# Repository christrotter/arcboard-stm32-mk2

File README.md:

# arcboard-stm32-mk2

Next iteration of the [STM32F405 mainboard](https://github.com/christrotter/arcboard-stm32).

## Features
- STM32F407 w. 12mHz HSE crystal
- 60x60mm footprint
- **60-pin FFC connector** for [the bespoke FFC loom](https://github.com/christrotter/arcboard-mk22-ffc)
  - Connects: 3x encoders, 4x6 keywell & 5 thumb keys, dpad, 3x paddle buttons, LCD, indicator LED PCBs, PMW3360
- **onboard button** for reset(*momentary*) and boot(*hold*) (*remote output also*)
- 128mb external **flash** via SPI (16MB)
- DRV2605L **haptic** driver via I2C, with PWM trigger (LRA or ERM)
- PAM8302A 2.5w **amplifier & piezo** (*or outputs*)
- 32kHz LSE crystal & **VBAT** wiring (*via external 1.8-3.3v battery*)
- **Two-layer** PCB & PCBA design for more affordable manufacturing
- Both USB connections have **ESD & power protection**
- Designed for **remote-mount** USB ports and boot/reset button
- **Split hand** GPIO via solder jumper
- **VBUS detection** via GPIO
- RGB-5v and LCD-3.3v supplies through MOSFET w. GPIO triggers
- WS2812 signal **level-shifted** to 5v
- Optional outputs
  - I2C
  - Debug
  - Haptic
  - Amplifier out
  - Ground + RGB-5v + WS2812 chain (*continuing from main loom*) for adding more LEDs (*e.g. aesthetic, underglow, etc*)
  - **Limit switch** (pull-up) output

## Improvements
- 100-pin CPU package offers much more flexibility, more options when wiring up the board
- The only soldering required is for JST-PH connectors (*2.0mm pin spacing*)
- Smaller diode package and setup saves space, keeps us on two-layer
- Actually working DFU system this time (*bad LCD pcb caused problems*)
- Fixed a number of issues, including mysterious overheating caused by a poor quality Schottky diode (*and bad spec choice on my part*)
- Inkscape-designed back silkscreen

## QMK notes
- I'm using `ROW2COL` because the Cyboard pcb's are designed this way.

## PCB/PCBA cost
My costs for getting the board made and assembled by JLC, to give you an idea of what this would cost to have built for you.

| Item | Cost (CAD) |
|---|---:|
| Setup fee | $25.56 |
| Stencil | $8.21 |
| Components | $67.86 |
| Extended components fee | $53.55 |
| SMT Assembly | $3.75 |
| Packaging fee | $0.49 |
| Advanced Options | $0.82 |
| Confirm Parts Placement | $0.45 |

## Bill of Materials (BOM)

| Designator | Footprint | Quantity | Value | LCSC Part # |
|---|---|---:|---|---|
| C1, C10, C20, C23 | 0805 | 4 | 4.7uF | C1779 |
| C11, C12, C14, C17, C18, C19, C26, C28, C5, C7, C8, C9 | 0402 | 12 | 100nF | C1525 |
| C13, C15, C2, C24, C27, C4 | 0402 | 6 | 1uF | C52923 |
| C16, C21 | 0402 | 2 | 2.2uF | C12530 |
| C22 | C0603 | 1 | CL10A106MA8NRNC | C96446 |
| C25 | C0805 | 1 | GCM21BR70J106KE22L | C126230 |
| C29, C3, C30, C6 | 0402 | 4 | 12p | C1547 |
| D1 | SMA_L4.3-W2.6-LS5.2-RD | 1 | SS34 | C8678 |
| D10, D11, D2, D3, D6, D8, D9 | X1-DFN1006-2_L1.0-W0.6-RD | 7 | CDSQC4148-HF | C6341459 |
| D4 | SOD-123FL_L2.8-W1.8-LS3.7-BI | 1 | SMF5_0CA_C364279 | C364279 |
| D5, D7 | SOT-666-6_L1.6-W1.2-P0.50-LS1.6-BL | 2 | USBLC6-2P6_C2827693 | C2827693 |
| F2 | F1206 | 1 | 1206L150SLYR | C207037 |
| F3 | F1206 | 1 | MF-NSMF075-2 | C89653 |
| L1 | L0805 | 1 | MPZ2012S101AT000 | C15957 |
| LED-LVL1 | SOT-563_L1.6-W1.2-P0.50-LS1.6-BR | 1 | SN74LVC1T45DRL | C352970 |
| MOSFET1, MOSFET3, MOSFET4 | SOT-23_L2.9-W1.3-P1.90-LS2.4-BR | 3 | AO3401A | C15127 |
| R1 | 0402 | 1 | 0402WGF1004TCE | C26083 |
| R10 | 0402 | 1 | 5.1k | C25905 |
| R11, R12, R16, R17, R2, R3, R5 | 0402 | 7 | 10k | C25744 |
| R4, R7, R8 | R0402 | 3 | 0402WGF4701TCE | C25900 |
| R14 | 0402 | 1 | 0402WGF1000TCE | C25076 |
| R15 | 0402 | 1 | 0402WGF1001TCE | C11702 |
| R6 | R0603 | 1 | 0603WAF3303T5E | C23137 |
| R9 | 0402 | 1 | 0402WGF1003TCE | C25741 |
| U1 | SOT-23-5 | 1 | XC6210B332MR-G | C82942 |
| U10, U9 | SOT-23-3_L2.9-W1.3-P1.90-LS2.4-BR | 2 | MMUN2233LT1G | C86932 |
| U13, U4 | SOT-23-3_L2.9-W1.3-P1.90-LS2.4-BR | 2 | 2N7002 | C8545 |
| U14 | SOIC-8_L5.3-W5.3-P1.27-LS8.0-BL | 1 | W25Q128JVSIQTR | C97521 |
| U15 | SW-SMD_4P-L5.1-W5.1-P3.70-LS6.5-TL_H1.5 | 1 | TS-1187A-B-A-B | C318884 |
| U2 | LQFP-100_14x14mm_P0.5mm | 1 | STM32F407VGTx | C12345 |
| U3 | FPC-SMD_FH52-60S-0.5SH | 1 | FH52-60S-0_5SH | C224193 |
| U5 | VSSOP-10_L3.0-W3.0-P0.50-LS4.9-BL | 1 | DRV2605LDGSR | C527464 |
| U6 | MSOP-8_L3.0-W3.0-P0.65-LS5.0-BL | 1 | PAM8302AASCR | C113367 |
| U8 | OSC-SMD_L3.2-W1.5 | 1 | SC-32S32_768kHz20PPM7pF | C97604 |
| Y1 | CRYSTAL-SMD_4P-L3.2-W2.5-BL-1 | 1 | Crystal_GND24 | C9002 |

Total line items: 35  
Total component quantity: 77

## Renders

## PCB layout

## Schematic

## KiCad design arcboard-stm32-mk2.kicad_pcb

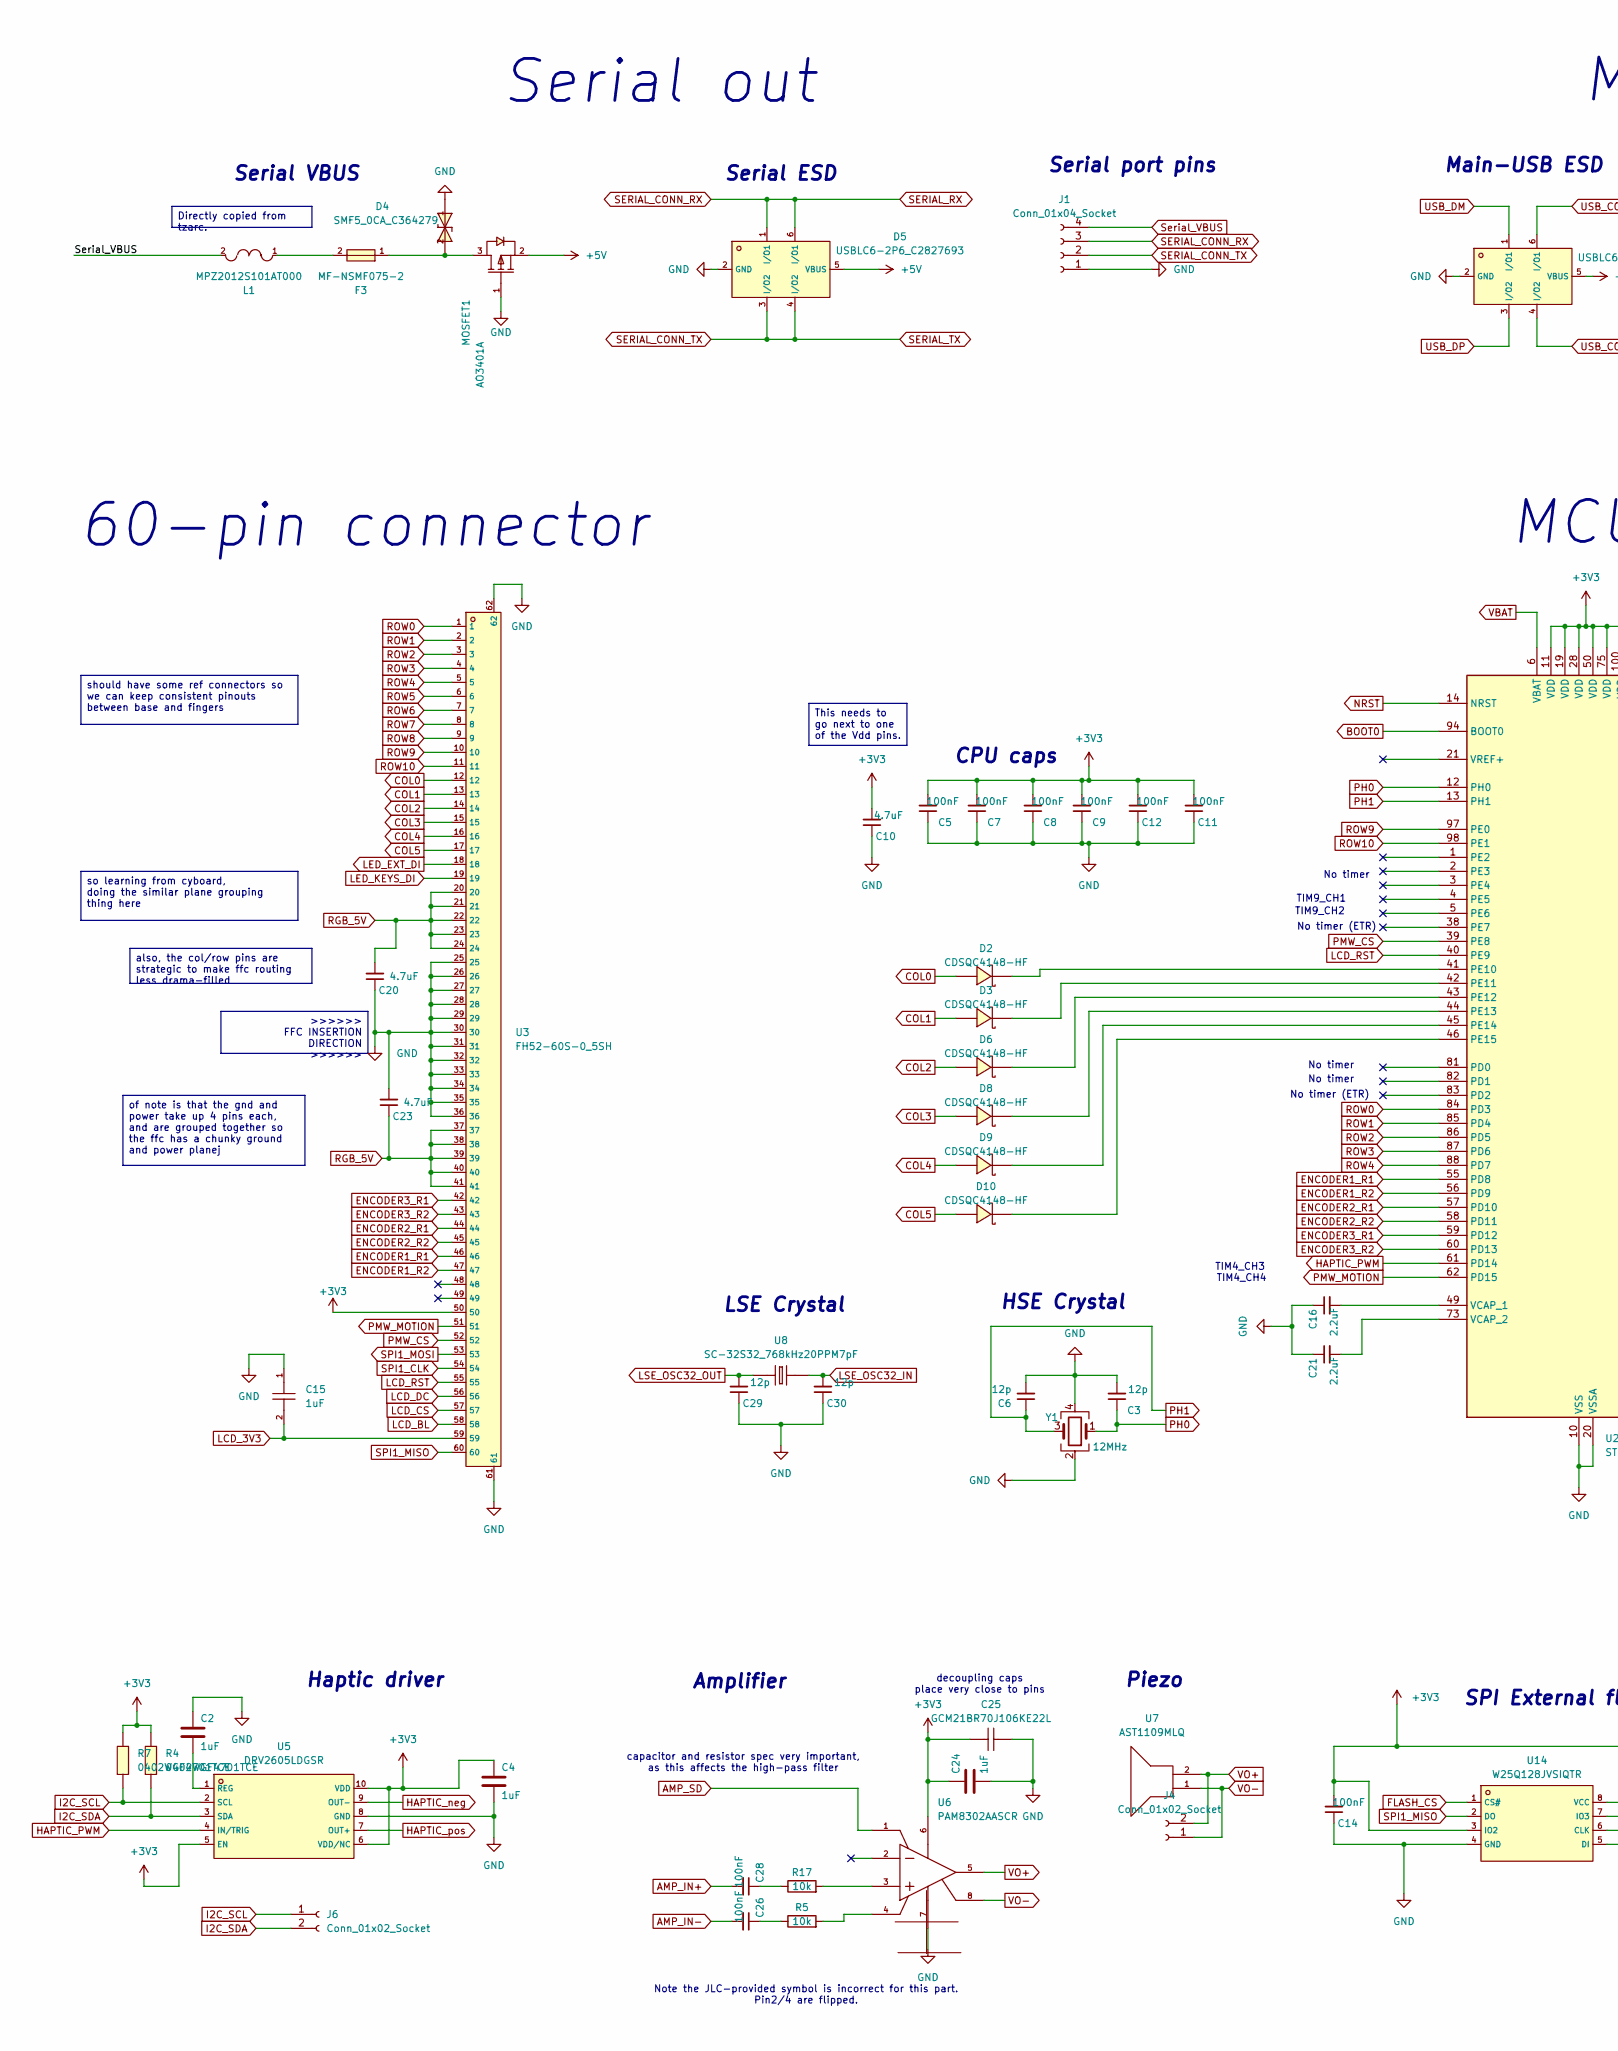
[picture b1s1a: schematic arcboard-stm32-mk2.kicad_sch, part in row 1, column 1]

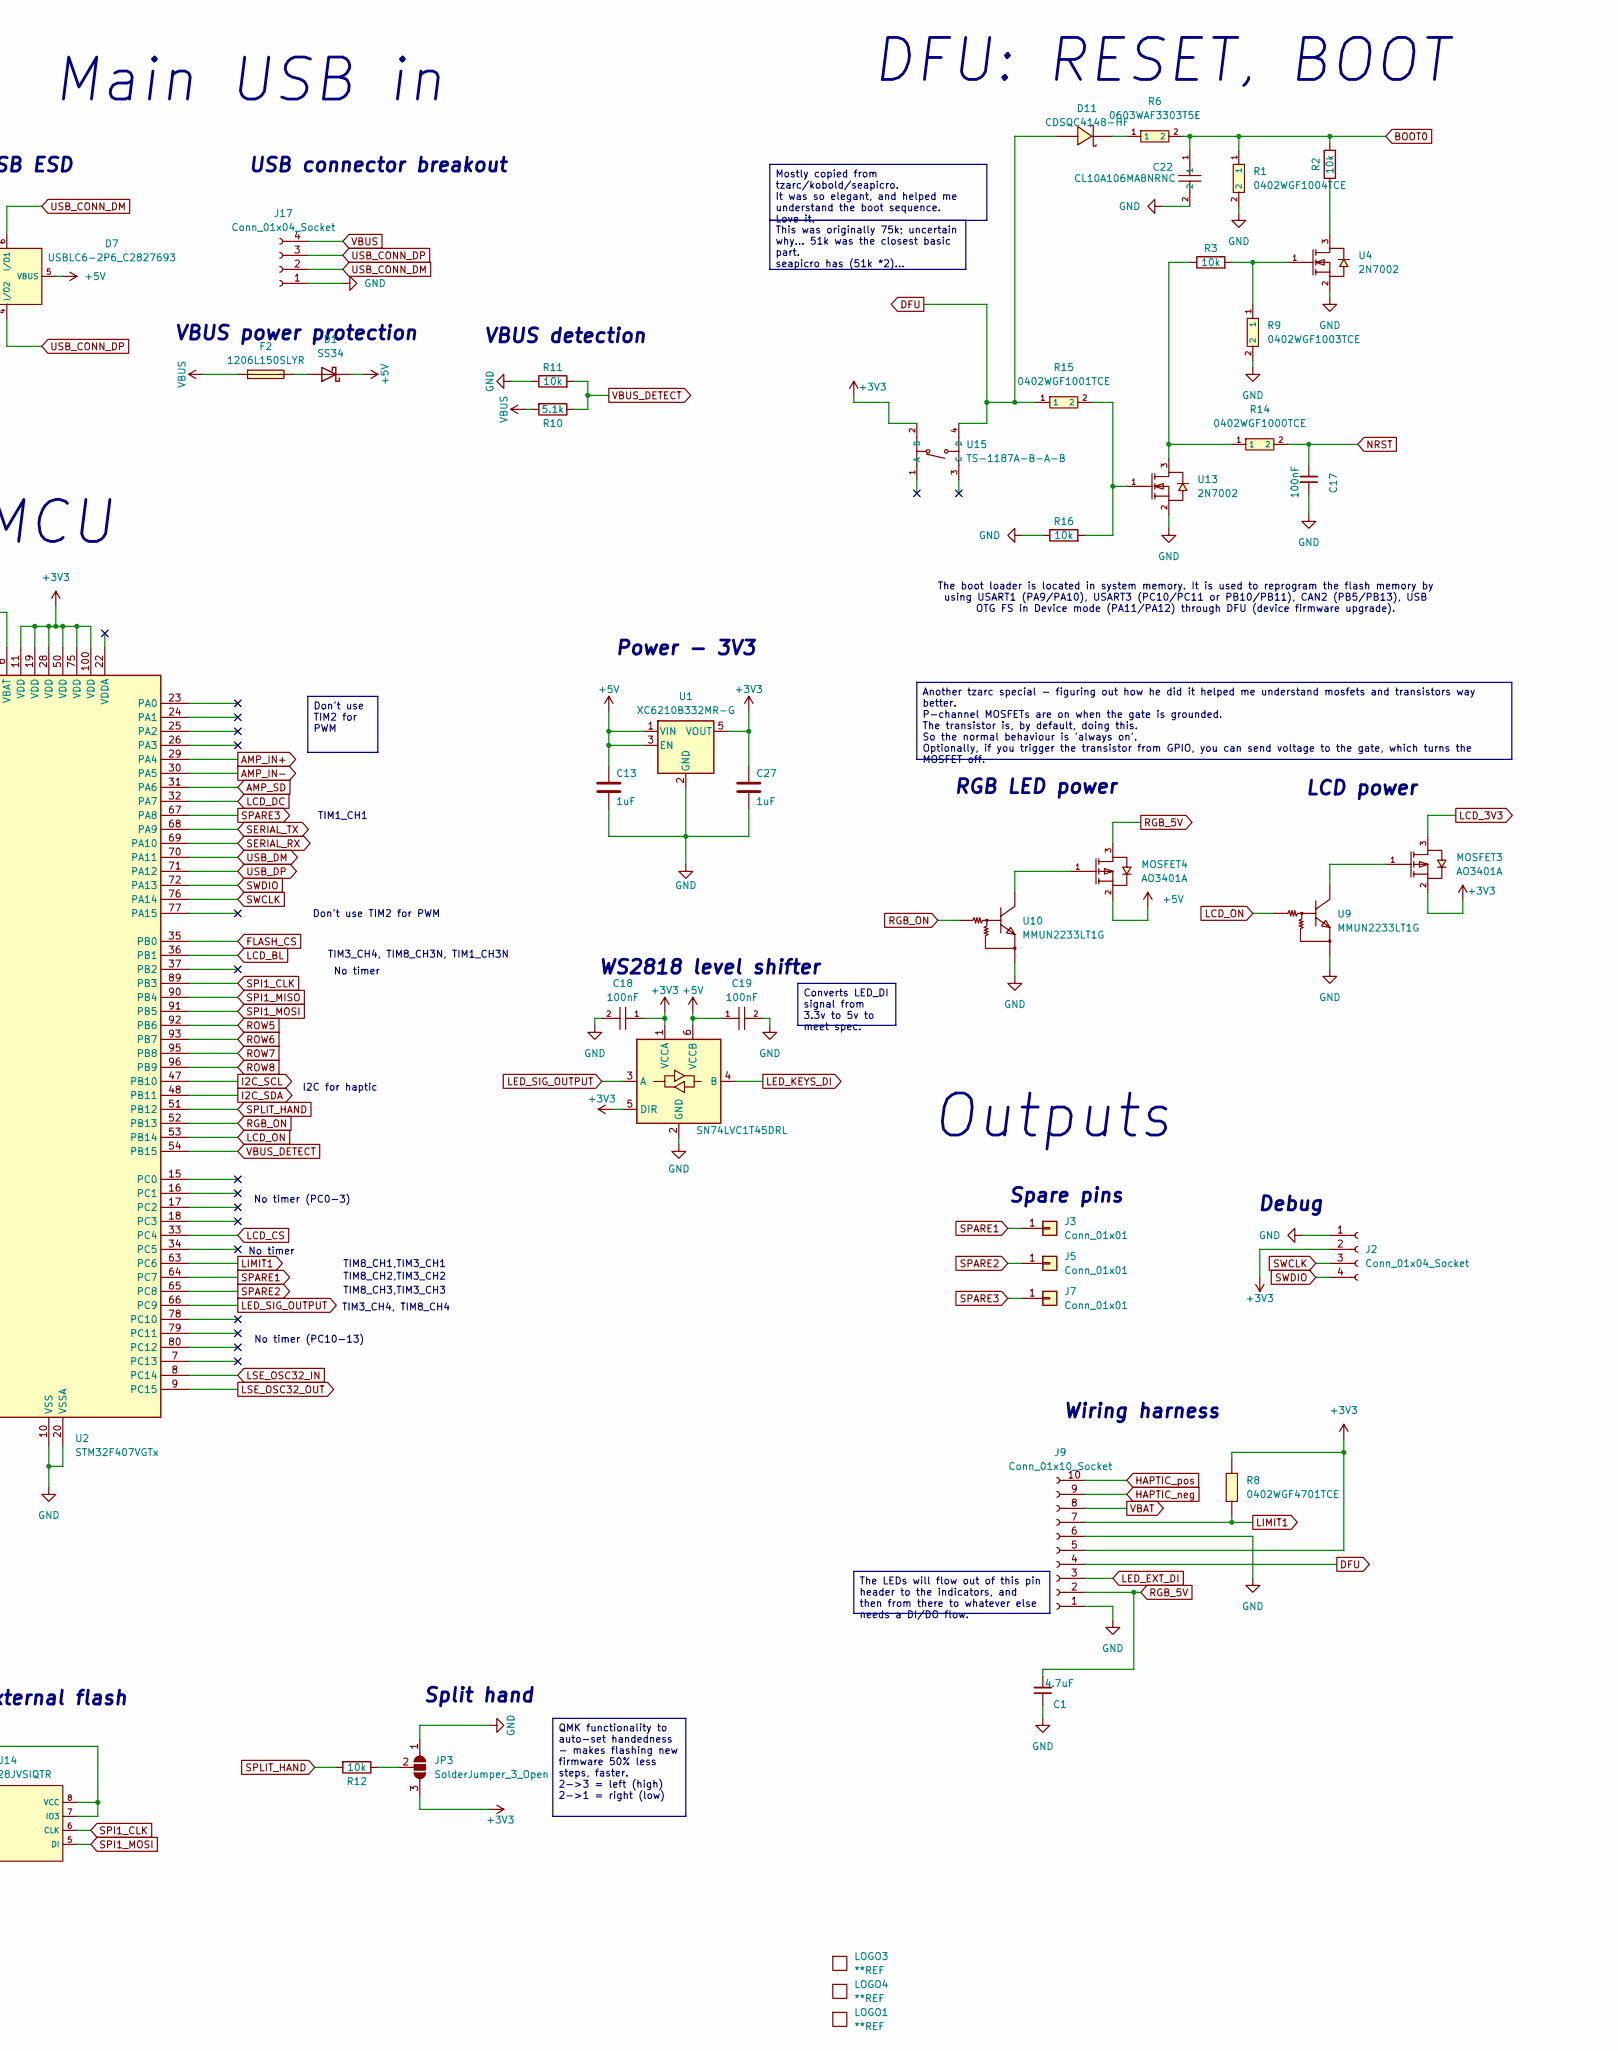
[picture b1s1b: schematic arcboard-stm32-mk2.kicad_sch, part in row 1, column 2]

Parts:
C1, C10, C20, C23: 4.7uF; C_0805_2012Metric; LCSC C1779
C2, C4, C13, C15, C24, C27: 1uF; C_0402_1005Metric; LCSC C52923
C3, C6, C29, C30: 12p; C_0402_1005Metric; LCSC C1547
C5, C7, C8, C9, C11, C12, C14, C17, C18, C19, C26, C28: 100nF; C_0402_1005Metric; LCSC C1525
C16, C21: 2.2uF; C_0402_1005Metric; LCSC C12530
C22: CL10A106MA8NRNC; C0603; LCSC C96446
C25: GCM21BR70J106KE22L; C0805; LCSC C126230
D1: SS34; SMA_L4.3-W2.6-LS5.2-RD; LCSC C8678
D2, D3, D6, D8, D9, D10, D11: CDSQC4148-HF; X1-DFN1006-2_L1.0-W0.6-RD; LCSC C6341459
D4: SMF5_0CA_C364279; SOD-123FL_L2.8-W1.8-LS3.7-BI; LCSC C364279
D5, D7: USBLC6-2P6_C2827693; SOT-666-6_L1.6-W1.2-P0.50-LS1.6-BL; LCSC C2827693
F2: 1206L150SLYR; F1206; LCSC C207037
F3: MF-NSMF075-2; F1206; LCSC C89653
J1, J17: Conn_01x04_Socket; JST_PH_S4B-PH-K_1x04_P2.00mm_Horizontal
J2: Conn_01x04_Socket; PinSocket_1x04_P1.00mm_Vertical
J3, J5, J7: Conn_01x01; TestPoint_Pad_1.5x1.5mm
J4: Conn_01x02_Socket; JST_PH_S2B-PH-K_1x02_P2.00mm_Horizontal
J6: Conn_01x02_Socket; PinHeader_1x02_P1.00mm_Vertical
J9: Conn_01x10_Socket; JST_PH_S10B-PH-K_1x10_P2.00mm_Horizontal
JP3: SolderJumper_3_Open; SolderJumper-3_P1.3mm_Open_Pad1.0x1.5mm
L1: MPZ2012S101AT000; L0805; LCSC C15957
LED-LVL1: SN74LVC1T45DRL; SOT-563_L1.6-W1.2-P0.50-LS1.6-BR; MPN SN74LVC1T45DRLR; JLC Basic N
LOGO1: **REF; awesome-logo
LOGO3: **REF; cyboard-logo-10mm
LOGO4: **REF; qmk-lite
MOSFET1, MOSFET3, MOSFET4: AO3401A; SOT-23_L2.9-W1.3-P1.90-LS2.4-BR; LCSC C15127
R1: 0402WGF1004TCE; R_0402_1005Metric; LCSC C26083
R2, R3, R5, R11, R12, R16, R17: 10k; R_0402_1005Metric; LCSC C25744
R4, R7, R8: 0402WGF4701TCE; R0402; LCSC C25900
R6: 0603WAF3303T5E; R0603; LCSC C23137
R9: 0402WGF1003TCE; R_0402_1005Metric; LCSC C25741
R10: 5.1k; R_0402_1005Metric; LCSC C25905
R14: 0402WGF1000TCE; R_0402_1005Metric; LCSC C25076
R15: 0402WGF1001TCE; R_0402_1005Metric; LCSC C11702
U1: XC6210B332MR-G; SOT-23-5; LCSC C82942
U2: STM32F407VGTx; LQFP-100_14x14mm_P0.5mm; LCSC C12345
U3: FH52-60S-0_5SH; FPC-SMD_FH52-60S-0.5SH; LCSC C224193
U4, U13: 2N7002; SOT-23-3_L2.9-W1.3-P1.90-LS2.4-BR; LCSC C8545
U5: DRV2605LDGSR; VSSOP-10_L3.0-W3.0-P0.50-LS4.9-BL; LCSC C527464
U6: PAM8302AASCR; MSOP-8_L3.0-W3.0-P0.65-LS5.0-BL; LCSC C113367
U7: AST1109MLQ; BUZ-SMD_L11.0-W9.0; LCSC C9900020429
U8: SC-32S32_768kHz20PPM7pF; OSC-SMD_L3.2-W1.5; LCSC C97604
U9, U10: MMUN2233LT1G; SOT-23-3_L2.9-W1.3-P1.90-LS2.4-BR; LCSC C86932
U14: W25Q128JVSIQTR; SOIC-8_L5.3-W5.3-P1.27-LS8.0-BL; LCSC C97521
U15: TS-1187A-B-A-B; SW-SMD_4P-L5.1-W5.1-P3.70-LS6.5-TL_H1.5; LCSC C318884
Y1: Crystal_GND24; CRYSTAL-SMD_4P-L3.2-W2.5-BL-1; LCSC C9002

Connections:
+3V3: C4.1, C5.2, C7.2, C8.2, C9.2, C10.2, C11.2, C12.2, C14.2, C18.1, C24.1, C25.1, C27.1, J2.2, J9.5, JP3.3 (B), LED-LVL1.1 (VCCA), LED-LVL1.5 (DIR), MOSFET3.2 (S), R4.2, R7.2, R8.2, U1.5 (VOUT), U2.11 (VDD), U2.19 (VDD), U2.28 (VDD), U2.50 (VDD), U2.75 (VDD), U2.100 (VDD), U3.50, U5.5 (EN), U5.6 (VDD/NC), U5.10 (VDD), U6.6 (VDD), U14.3 (IO2), U14.7 (IO3), U14.8 (VCC), U15.2 (B)
+5V: C13.1, C19.1, D1.1 (K), D5.5 (VBUS), D7.5 (VBUS), LED-LVL1.6 (VCCB), MOSFET1.2 (S), MOSFET4.2 (S), U1.1 (VIN), U1.3 (EN)
AMP_IN+: C28.2, U2.29 (PA4)
AMP_IN-: C26.2, U2.30 (PA5)
AMP_SD: U2.31 (PA6), U6.1 (SD#)
BOOT0: C22.1, R1.1, R2.2, R6.2, U2.94 (BOOT0)
COL0: D2.2 (A), U3.12
COL1: D3.2 (A), U3.13
COL2: D6.2 (A), U3.14
COL3: D8.2 (A), U3.15
COL4: D9.2 (A), U3.16
COL5: D10.2 (A), U3.17
DFU: D11.2 (A), J9.4, R15.1, U15.4 (D)
ENCODER1_R1: U2.55 (PD8), U3.46
ENCODER1_R2: U2.56 (PD9), U3.47
ENCODER2_R1: U2.57 (PD10), U3.44
ENCODER2_R2: U2.58 (PD11), U3.45
ENCODER3_R1: U2.59 (PD12), U3.42
ENCODER3_R2: U2.60 (PD13), U3.43
FLASH_CS: U2.35 (PB0), U14.1 (CS#)
GND: C1.1, C2.1, C3.2, C4.2, C5.1, C6.2, C7.1, C8.1, C9.1, C10.1, C11.1, C12.1, C13.2, C14.1, C15.1, C16.1, C17.1, C18.2, C19.2, C20.1, C21.1, C22.2, C23.2, C24.2, C25.2, C27.2, C29.1, C30.1, D4.1 (K), D5.2 (GND), D7.2 (GND), J1.1, J2.1, J9.1, J9.6, J17.1, JP3.1 (A), LED-LVL1.2 (GND), MOSFET1.1 (G), R1.2, R9.2, R11.1, R16.1, U1.2 (GND), U2.10 (VSS), U2.20 (VSSA), U2.27 (VSS), U2.74 (VSS), U2.99 (VSS), U3.25, U3.26, U3.27, U3.28, U3.29, U3.30, U3.31, U3.32, U3.33, U3.34, U3.35, U3.36, U3.61, U3.62, U4.2 (S), U5.8 (GND), U6.7 (GND), U9.2 (E), U10.2 (E), U13.2 (S), U14.4 (GND), Y1.2, Y1.4
HAPTIC_PWM: U2.61 (PD14), U5.4 (IN/TRIG)
HAPTIC_neg: J9.9, U5.9 (OUT-)
HAPTIC_pos: J9.10, U5.7 (OUT+)
I2C_SCL: J6.1, R7.1, U2.47 (PB10), U5.2 (SCL)
I2C_SDA: J6.2, R4.1, U2.48 (PB11), U5.3 (SDA)
LCD_3V3: C15.2, MOSFET3.3 (D), U3.59
LCD_BL: U2.36 (PB1), U3.58
LCD_CS: U2.33 (PC4), U3.57
LCD_DC: U2.32 (PA7), U3.56
LCD_ON: U2.53 (PB14), U9.1 (B)
LCD_RST: U2.40 (PE9), U3.55
LED_EXT_DI: J9.3, U3.18
LED_KEYS_DI: LED-LVL1.4 (B), U3.19
LED_SIG_OUTPUT: LED-LVL1.3 (A), U2.66 (PC9)
LIMIT1: J9.7, R8.1, U2.63 (PC6)
LSE_OSC32_IN: C30.2, U2.8 (PC14), U8.2
LSE_OSC32_OUT: C29.2, U2.9 (PC15), U8.1
NRST: C17.2, R14.2, U2.14 (NRST)
unnamed: C26.1, R5.1
unnamed: C28.1, R17.1
unnamed: D1.2 (A), F2.2
unnamed: D2.1 (K), U2.41 (PE10)
unnamed: D3.1 (K), U2.42 (PE11)
unnamed: D4.2 (A), F3.1, MOSFET1.3 (D)
unnamed: D6.1 (K), U2.43 (PE12)
unnamed: D8.1 (K), U2.44 (PE13)
unnamed: D9.1 (K), U2.45 (PE14)
unnamed: D10.1 (K), U2.46 (PE15)
unnamed: D11.1 (K), R6.1
unnamed: F3.2, L1.1
unnamed: JP3.2 (C), R12.1
unnamed: MOSFET3.1 (G), U9.3 (C)
unnamed: MOSFET4.1 (G), U10.3 (C)
unnamed: C16.2, U2.49 (VCAP_1)
unnamed: C21.2, U2.73 (VCAP_2)
unnamed: R2.1, U4.3 (D)
unnamed: R3.2, R9.1, U4.1 (G)
unnamed: C2.2, U5.1 (REG)
unnamed: R17.2, U6.3 (IN+)
unnamed: R5.2, U6.4 (IN-)
unnamed: R3.1, R14.1, U13.3 (D)
unnamed: R15.2, R16.2, U13.1 (G)
PH0: C3.1, U2.12 (PH0), Y1.1
PH1: C6.1, U2.13 (PH1), Y1.3
PMW_CS: U2.39 (PE8), U3.52
PMW_MOTION: U2.62 (PD15), U3.51
RGB_5V: C1.2, C20.2, C23.1, J9.2, MOSFET4.3 (D), U3.20, U3.21, U3.22, U3.23, U3.24, U3.37, U3.38, U3.39, U3.40, U3.41
RGB_ON: U2.52 (PB13), U10.1 (B)
ROW0: U2.84 (PD3), U3.1
ROW1: U2.85 (PD4), U3.2
ROW2: U2.86 (PD5), U3.3
ROW3: U2.87 (PD6), U3.4
ROW4: U2.88 (PD7), U3.5
ROW5: U2.92 (PB6), U3.6
ROW6: U2.93 (PB7), U3.7
ROW7: U2.95 (PB8), U3.8
ROW8: U2.96 (PB9), U3.9
ROW9: U2.97 (PE0), U3.10
ROW10: U2.98 (PE1), U3.11
SERIAL_CONN_RX: D5.1 (I/O1), D5.6 (I/O1), J1.3, U2.69 (PA10)
SERIAL_CONN_TX: D5.3 (I/O2), D5.4 (I/O2), J1.2, U2.68 (PA9)
SPARE1: J3.1, U2.64 (PC7)
SPARE2: J5.1, U2.65 (PC8)
SPARE3: J7.1, U2.67 (PA8)
SPI1_CLK: U2.89 (PB3), U3.54, U14.6 (CLK)
SPI1_MISO: U2.90 (PB4), U3.60, U14.2 (DO)
SPI1_MOSI: U2.91 (PB5), U3.53, U14.5 (DI)
SPLIT_HAND: R12.2, U2.51 (PB12)
SWCLK: J2.3, U2.76 (PA14)
SWDIO: J2.4, U2.72 (PA13)
Serial_VBUS: J1.4, L1.2
USB_CONN_DM: D7.6 (I/O1), J17.2
USB_CONN_DP: D7.4 (I/O2), J17.3
USB_DM: D7.1 (I/O1), U2.70 (PA11)
USB_DP: D7.3 (I/O2), U2.71 (PA12)
VBAT: J9.8, U2.6 (VBAT)
VBUS: F2.1, J17.4, R10.2
VBUS_DETECT: R10.1, R11.2, U2.54 (PB15)
VO+: J4.2, U6.5 (VO+), U7.2
VO-: J4.1, U6.8 (VO-), U7.1

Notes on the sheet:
No timer (PC10-13)
Amplifier
LSE Crystal
TIM9_CH2
DFU: RESET, BOOT
TIM8_CH3,TIM3_CH3
Serial VBUS
I2C for haptic
No timer
TIM3_CH4, TIM8_CH4
TIM8_CH2,TIM3_CH2
Serial port pins
Outputs
USB connector breakout
Don't use TIM2 for PWM
No timer (ETR)
TIM1_CH1
decoupling caps place very close to pins
HSE Crystal
Main USB in
TIM8_CH1,TIM3_CH1
CPU caps
No timer (PC0-3)
VBUS detection
RGB LED power
Wiring harness
SPI External flash
Piezo
Power - 3V3
TIM9_CH1
TIM3_CH4, TIM8_CH3N, TIM1_CH3N
Note the JLC-provided symbol is incorrect for this part. Pin2/4 are flipped.
LCD power
Spare pins
60-pin connector
WS2818 level shifter
Split hand
Haptic driver
capacitor and resistor spec very important, as this affects the high-pass filter
TIM4_CH4

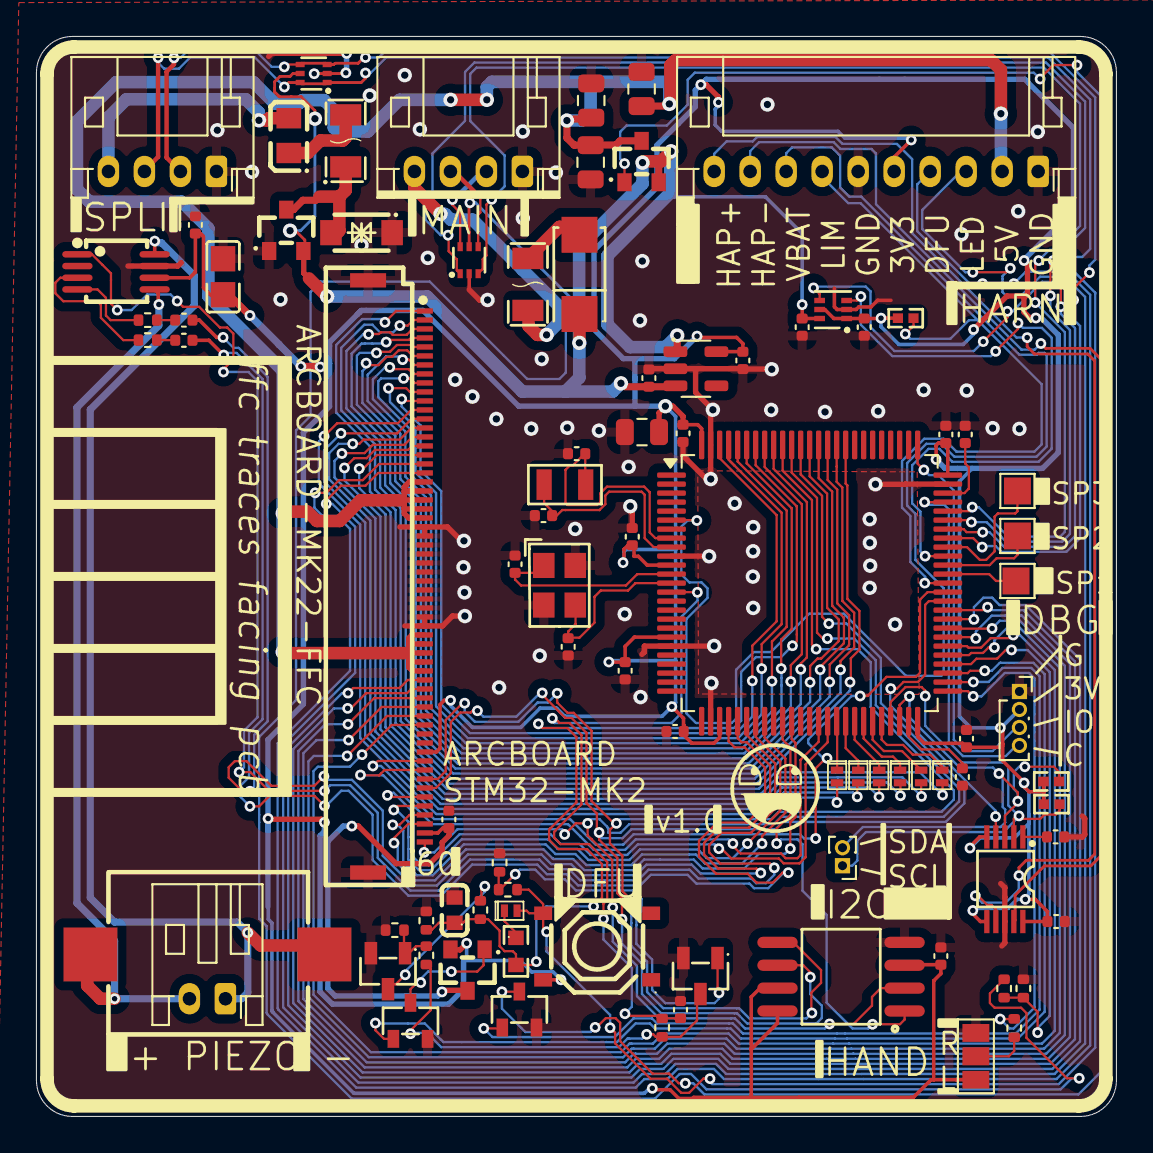
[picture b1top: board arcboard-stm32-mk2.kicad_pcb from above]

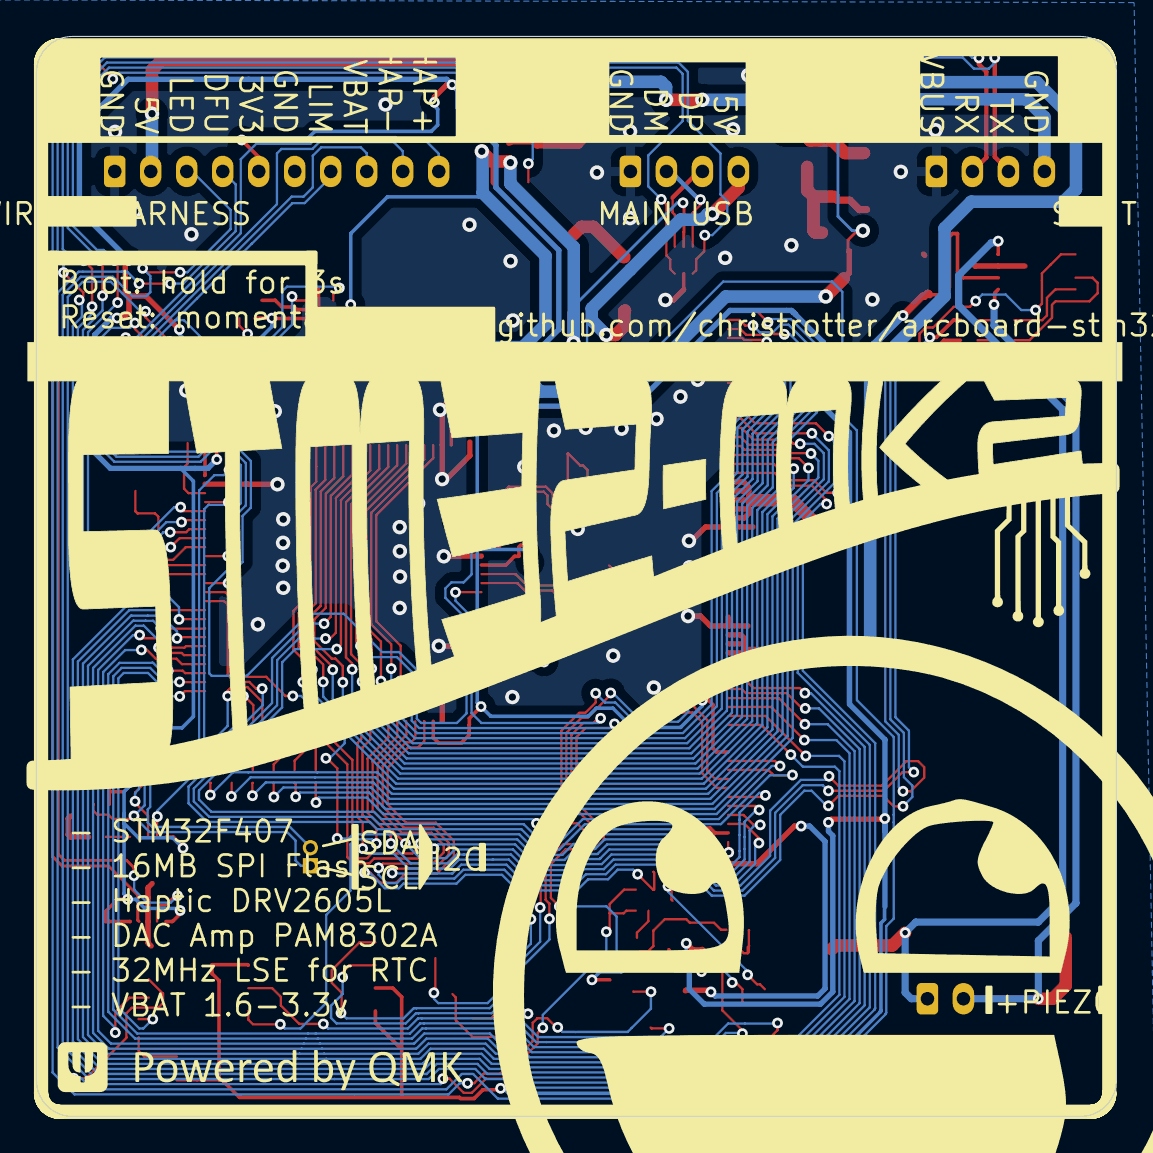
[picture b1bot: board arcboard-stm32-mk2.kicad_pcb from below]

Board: 2 copper layers, 60.0 x 60.0 mm, 91 parts (2 on the bottom side), 101 nets.

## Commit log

2026-05-31 adding first draft kicad files
2026-06-01 starting readme, added haptic
2026-06-01 finishing haptic bits
2026-06-01 adding dac amp
2026-06-02 adding piezo that does not fit
2026-06-02 re-organized the bottom section to fit a piezo
2026-06-03 silkscreen work, adding lse crystal and vbat hookup
2026-06-04 fixing issues brought up by drashna, adding timer notation to schematic
2026-06-04 improving top silkscreen
2026-06-04 top silkscreen good enough for now
2026-06-05 silkscreen mostly done, fixed some DRC issues
2026-06-05 tidying up ground planes, traces
2026-06-05 fixing haptic driver missing another vdd, more
2026-06-05 adding images
2026-06-05 first iteration of readme
2026-06-05 moving i2c breakout to not interfere with rear silkscreen, moving piezo b.silk label
2026-06-06 refactoring rgb-lcd power to match tzarc, old way was fundamentally broken
2026-06-06 silkscreen refactoring and moving bits around
2026-06-06 improved polyfuse part, fixing critical amplifier symbol mistake, other re-ordering
2026-06-06 almost ready for ordering
2026-06-09 fixing i2c resistors, prepping for 10pin
2026-06-23 bunch o updates
